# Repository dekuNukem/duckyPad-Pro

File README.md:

# duckyPad Pro: Advanced Macro Scripting Beyond QMK/VIA

[Get duckyPad Pro](https://www.tindie.com/products/37399/) | [Official Discord](https://discord.gg/4sJCBx5) | [Getting Started](./doc/getting_started.md) | [Table of Contents](#table-of-contents)

-----------

duckyPad Pro is a 20-key **mechanical macropad** for power users who demand **advanced macro scripting and customisation** beyond the shackles of QMK/VIA.

Using a [Turing-complete scripting language](https://dekunukem.github.io/duckyPad-Pro/doc/duckyscript_info.html) with **massive on-board storage**, it can automate **any keyboard/mouse input** you want, from **simple combos** to **full-blown programs**.

## Get One

duckyPad Pro has been [successfully funded on Kickstarter](https://www.kickstarter.com/projects/dekunukem/duckypad-pro-advanced-macro-scripting-beyond-qmk-via) with more than $100K raised!

* Now available [on my Store!](https://www.tindie.com/products/37399/)

No drivers needed. Works anywhere.

## Highlights

duckyPad Pro has all the basics:

* Hot-Swap
* Rotary Encoders (**Tactile or Smooth**)
* Per-key RGB
* 100% **Open-source**

But also features **unlike any other**:

* Custom **[duckyScript](https://dekunukem.github.io/duckyPad-Pro/doc/duckyscript_info.html)** engine, **NOT QMK/VIA**.
* **Longer and more complex** macros
	* **64 profiles**, 3712 macros.
* **OLED** screen
* **Bluetooth**
* Real-time Clock (RTC)
* **[Expansion Modules](https://github.com/dekuNukem/duckyPad-expansion-modules)** for external switches / foot pedals
* [Profile Auto-switching](https://github.com/dekuNukem/duckyPad-profile-autoswitcher) based on **active window**.
* microSD storage
* No proprietary drivers, works out-of-box.
* **Hacker friendly** with [tinkering guide](./doc/tinkering_guide.md)

## duckyScript vs QMK/VIA

duckyPad Pro runs **duckyScript**, originally designed for the [USB Rubber Ducky](https://shop.hak5.org/products/usb-rubber-ducky-deluxe).

Compared to QMK/VIA, you get:

* **Much Longer Macros**
	* [Entire Bee Movie](resources/beemovie.txt) in one macro? Sure thing!
	* Over 3700 macros total

* **Turing-Complete Scripting**
	* Variables, conditions, loops, functions, and more.
	* Executed on [32-bit Bytecode VM](https://duckypad.github.io/DuckStack/)
	* With **Scratch** and **Non-volatile Memory**

* **Advanced Interactions**
	* Reading Buttons
	* Print to OLED screen
	* Change RGB Color
	* How about a fully functional [Pong game?](resources/photos/pong.gif) [[code]](resources/pong.txt)

* **SD Card Storage**
	* Fast Configuration / Backup / Deployment
	* No sketchy drivers or apps
	* No recompiling

While QMK/VIA are great for regular keyboards, they are limited at input automations.

duckyScript is a no-brainer for **power users** with more demanding scripting needs.

## How It Works / Showcase

* Create up to **64 profiles**, one for each application.

* Assign up to **58 keys** per profile (20 onboard + 6 rotary encoder + 32 external)

* Names are shown on OLED screen

* Write a **duckyScript** for each key

### Easy Start

* **duckyScript** is a language for automating inputs

	* At simplest, you just tell it **what key to press!**

* Such as **key combos** of your favorite app

**Browsing**

Zoom In: `CTRL +`

Next Tab: `CTRL SHIFT TAB`

### Up a Notch

* Once familiar, you can write **longer multi-line macros** to further speed up everyday task.

* Such as **filling forms** and typing **boilerplate text** with one keypress.

```
STRING Michael Scott
TAB
STRING United States
ENTER
STRING 5705550100
TAB
STRING michael.scott@dundermifflin.com
TAB
```

Or a simple mouse jiggler:

```
WHILE TRUE
	MOUSE_MOVE $_RANDOM_INT $_RANDOM_INT
	DELAY 100
END_WHILE
```

### Full Potential

* Going all-out, duckyScript is a **Turing-Complete** **general-purpose** language.
* You can use it to:
	* Read Buttons
	* Write to OLED screen
	* Change RGB colors
	* Perform operations with **32-bit variables**, **conditions**, **loops**, **function call**s, and more!
* Write ultra-specific macros for your exact needs

```
RGB_SET 1 128 0 255

OLED_PRINT You are in a maze
OLED_PRINT of twisty little passages

VAR choice = _READKEY

IF choice == 1
    OLED_CURSOR 0 10
    OLED_PRINT It is a dead end.
    OLED_PRINT Something moves
    OLED_PRINT behind you.
END_IF
```

Or how about a fully working [Pong game?](resources/pong.txt)

```
WHILE TRUE
    active_key = _READKEY
    OLED_CLEAR
    draw_paddle()
    draw_court()
    draw_ball()
    OLED_UPDATE
    DELAY 20
END_WHILE
```

### Hackerman

* Of course, by automating inputs, you can take over an entire computer with the push of a button!

* This is known as [BadUSB attack](https://arstechnica.com/information-technology/2014/07/this-thumbdrive-hacks-computers-badusb-exploit-makes-devices-turn-evil/), and was the original purpose of [USB Rubber Ducky](https://shop.hak5.org/products/usb-rubber-ducky-deluxe).

---------

### Nothing Like It

* From **simple shortcuts** to **full-blown programs**, duckyScript can easily achieve what was impossible on QMK/VIA.

* Each macro can contain over **60,000 characters**

* Store over **3700 macros** in total

* Executed on custom [virtual stack machine](https://duckypad.github.io/DuckStack/)

## Bluetooth

duckyPad Pro also works as a **Bluetooth Keyboard & Mouse** (with a catch!)

* Bluetooth 5.0
* Built-in Antenna for both BT and Wi-Fi

**So what's the catch?**

* You need to provide your own USB battery bank

Yes I know it's a bit silly having BT without internal battery! However, it would involve more complex case design, additional components, and international shipping of rechargeable batteries.

All of which would inflate the cost way beyond just using an off-the-shelf battery pack.

As this is a one-person project, I prefer to keep things simple.

## Expansion Modules

duckyPad Pro also supports optional [expansion modules](https://github.com/dekuNukem/duckyPad-expansion-modules) for even more customisability.

* Wire up your own **switches / buttons / foot pedals**
* **8 channels** per module
* **Daisy-chain** up to 32 channels

## New CPU

duckyPad Pro now runs a significantly more powerful processor:

* ESP32-S3
* Dual-Core @ 240 MHz 
* 4MB Flash Memory
* 512KB RAM
* 2MB PSRAM

Switching to ESP32 also allows **much simpler setup for tinkering:**

* VSCode IDE
* Open-source toolchain
* USB Flashing, no external programmer needed.
* [Tinkering guide provided](./doc/tinkering_guide.md)

## QoL Updates

* Separate script for **on press** and **on release**
* **Abort execution** with any key
* Read `NUMLOCK` / `CAPSLOCK` / `SCROLLLOCK` status
* Switch profile by name (instead of number)
* Configurable screen orientation
* Mount SD Card as **USB Storage**
* Blocking `$_READKEY`
* Much faster configurator load/save
* **Drag & drop** firmware update
* More sturdy +/- button
* Reinforced hotswap socket solder pads
* A lot more under-the-hood optimizations

## duckyPad Configurator

[Use the open-source configurator](https://github.com/duckyPad/duckyPad-Configurator) to set up your duckyPad Pro.

* Windows | Mac | Linux
* No account / subscription needed
* No data collection / telemetry

## Profile Auto-switching

* [Automatically jump to the appropriate profile](https://github.com/dekuNukem/duckyPad-profile-autoswitcher)
* Based on **current active window**

## Mechanical Switches

duckyPad Pro has **20 Mechanical Switches** in **4x5 Grid.**

* Kailh hot-swap socket
* Cherry-MX compatible (Both 3 and 5-Pin)
* North-facing ARGB LED
* Configurable colour & brightness

## Rotary Encoders

* Two Encoders
* Bourns Inc. PEC12R Series
* Built-in Tactile Switch
* Max Knob Diameter: 24mm

## OLED Display

* 128x128
* 1.5 inch
* High contrast with true black
* **Configurable orientation**
* Burn-in Prevention

## Interested?

Available [on my store!](https://www.tindie.com/products/37399/)

Join our [Official Discord](https://discord.gg/4sJCBx5) for discussions and updates!

## Specifications

## Questions or Comments?

Please feel free to [open an issue](https://github.com/dekuNukem/duckypad-pro/issues), ask in the [official duckyPad discord](https://discord.gg/4sJCBx5), or email `dekuNukem`@`gmail`.`com`!

## Disclaimers

* duckyPad has been in active development since 2017, and every effort has been made to ensure its reliability. However, it is **NOT** designed or certified for safety-critical applications. Use at your own risk.

* Scripts are stored as **plain text** on the SD card. Keep in mind before including sensitive information.

* duckyScript appears to be a trademark of [Hak5 LLC](https://docs.hak5.org/hak5-usb-rubber-ducky/duckyscript-tm-quick-reference). The duckyPad project is not affiliated with, or endorsed by Hak5 LLC.

* The duckyScript [compiler and virtual machine](https://duckypad.github.io/DuckStack/) used in this project are independently developed from scratch.

## Table of Contents

[Main page](README.md)

[Getting Started Guide](./doc/getting_started.md)

[Kit Assembly Guide](./doc/kit_assembly.md)

[Writing duckyScript](./doc/duckyscript_info.md)

[duckStack VM](https://duckypad.github.io/DuckStack/)

[Tinkering Guide](./doc/tinkering_guide.md)

[Troubleshooting](./doc/troubleshooting.md)

[Firmware Update](./doc/fw_update.md)

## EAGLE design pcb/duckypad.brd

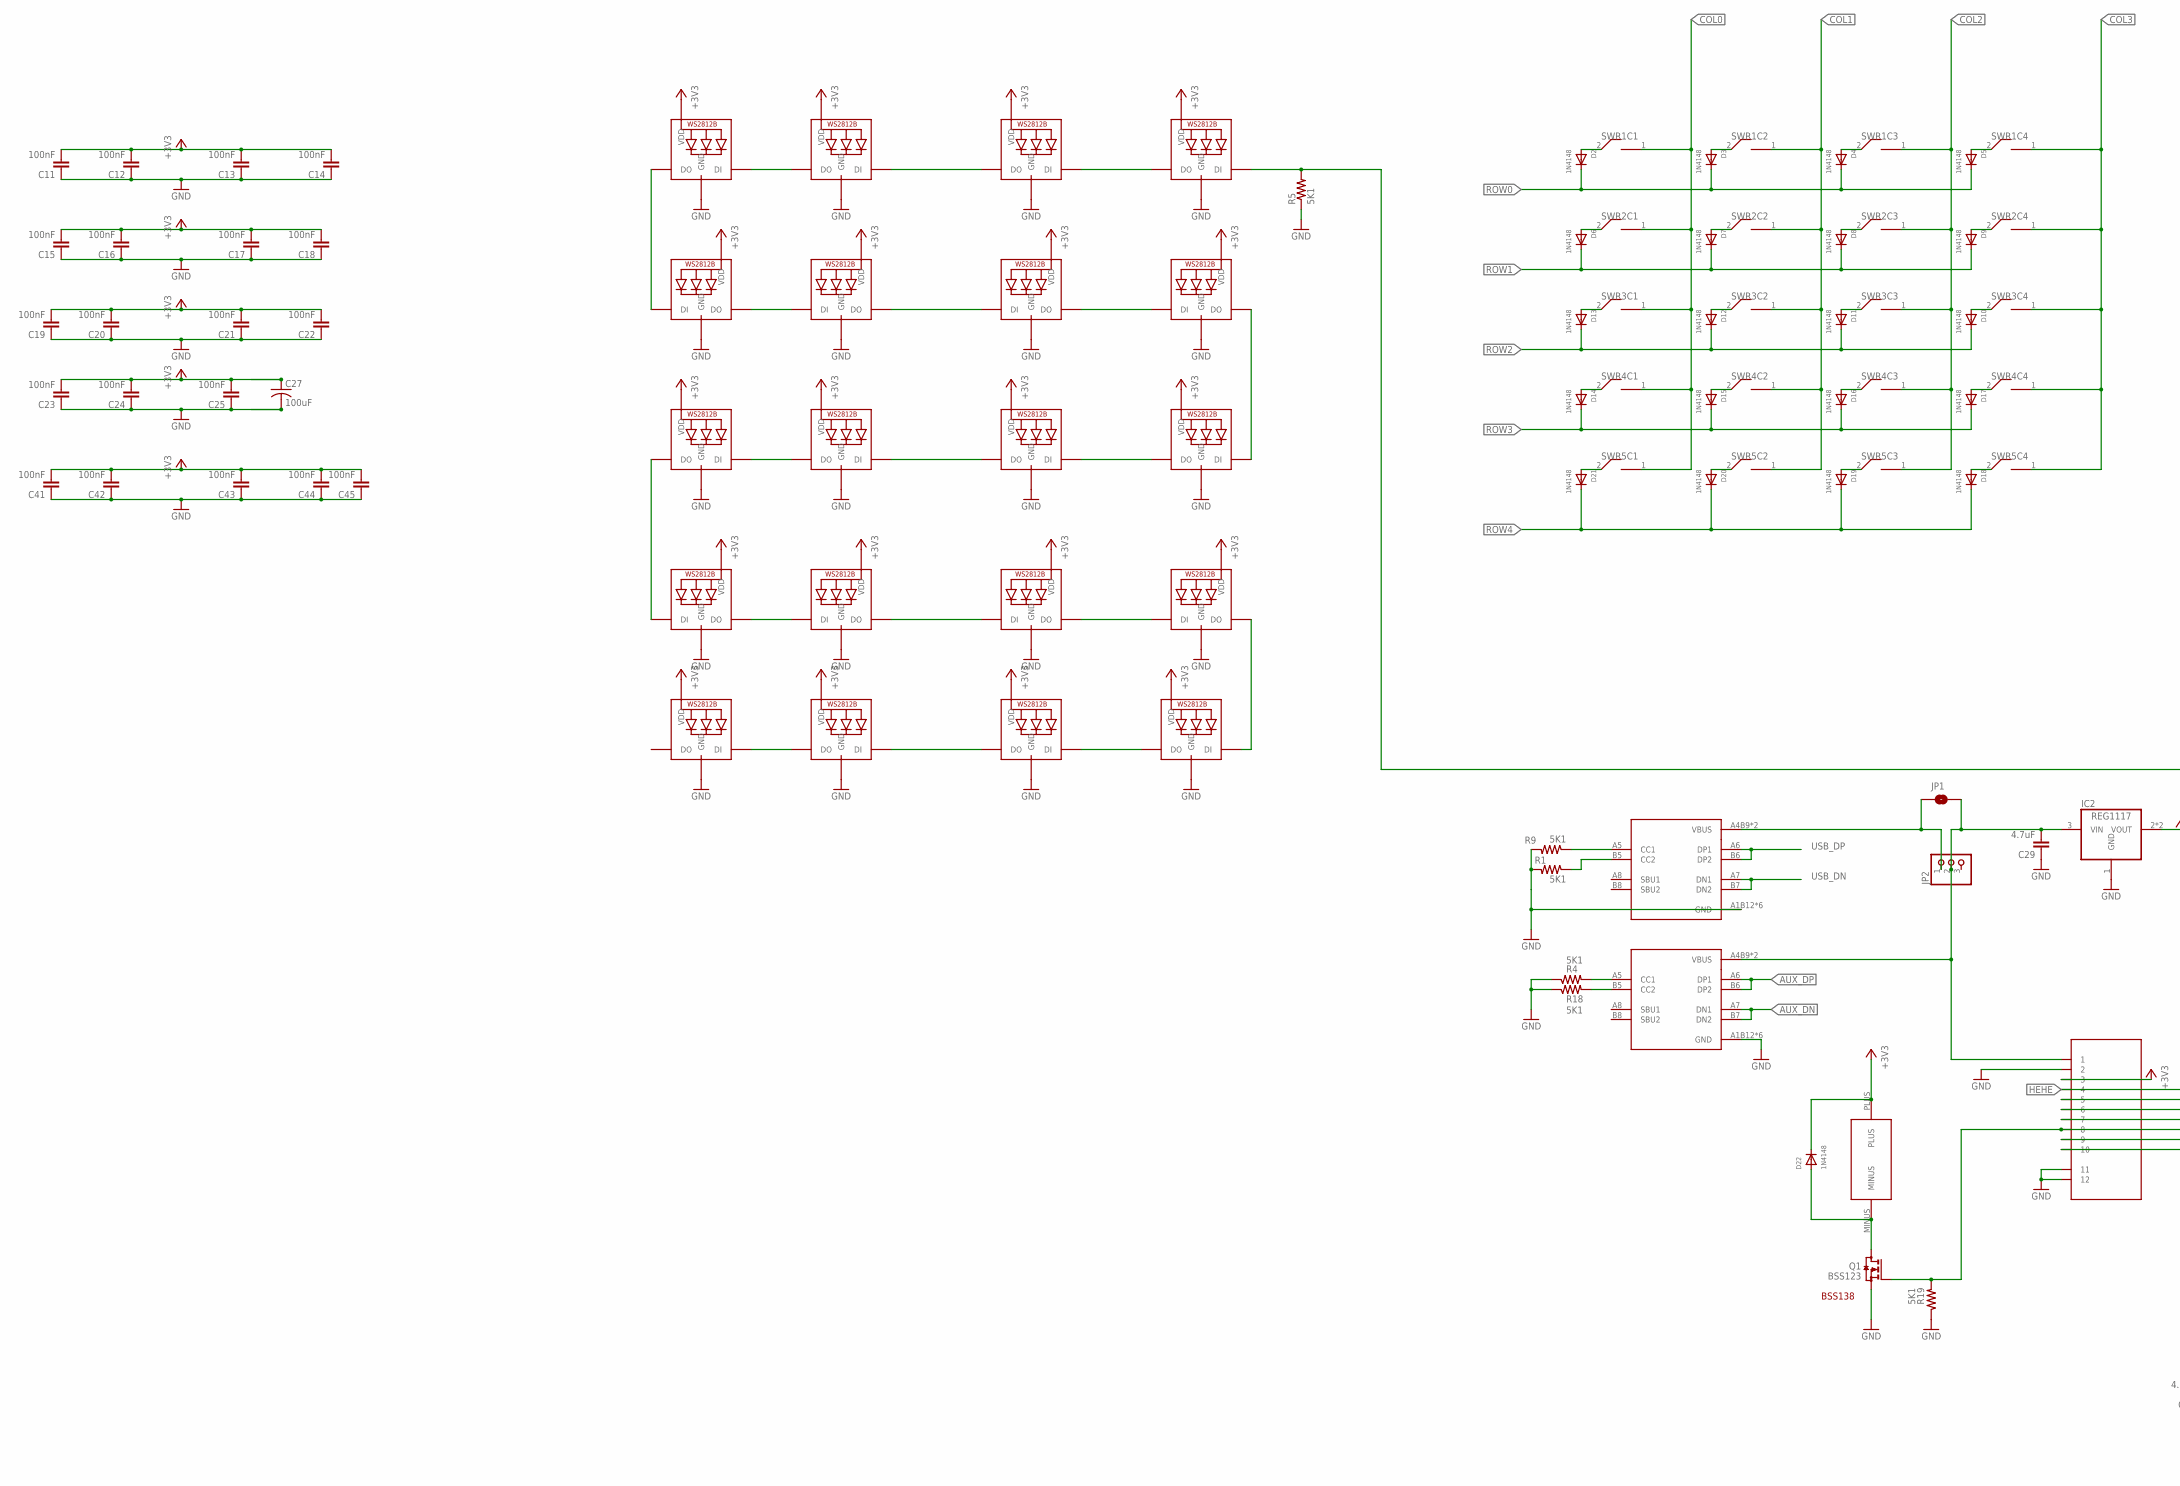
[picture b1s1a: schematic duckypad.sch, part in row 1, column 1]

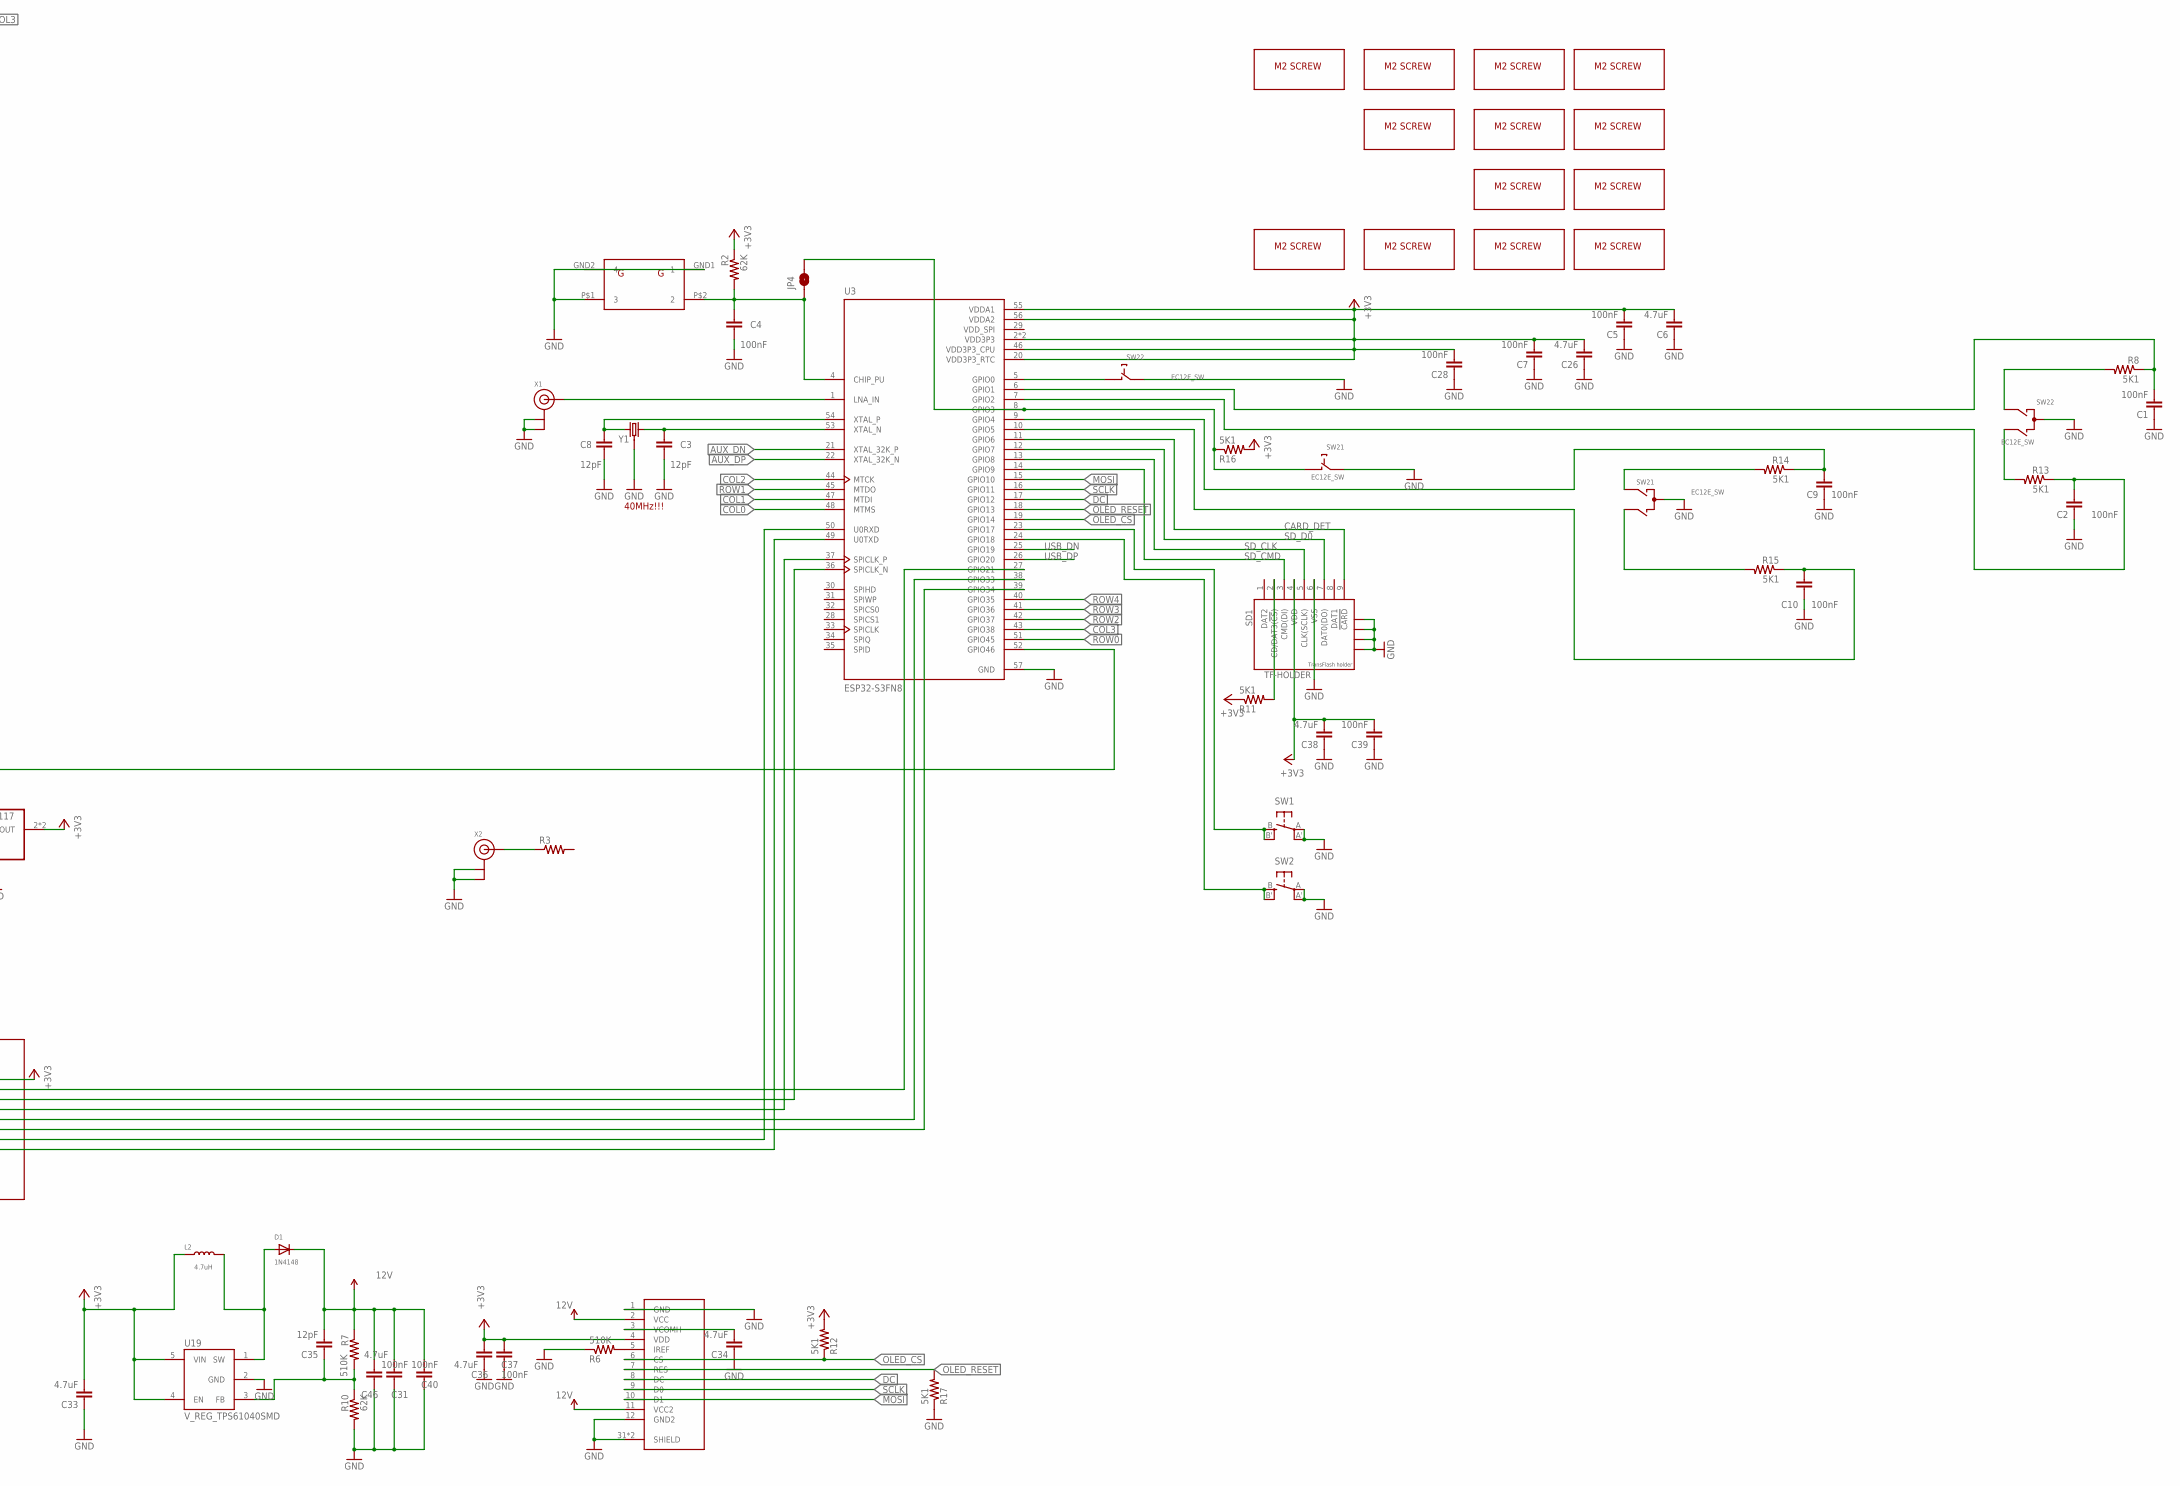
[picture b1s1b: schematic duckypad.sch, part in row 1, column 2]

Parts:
BZ1: BUZZ40402; BUZZ
C1, C2, C4, C5, C7, C9, C10, C11, C12, C13, C14, C15, C16, C17, C18, C19, C20, C21, C22, C23, C24, C25, C28, C31, C37, C39, C40, C41, C42, C43, C44, C45: 100nF; 0805
C3, C8, C35: 12pF; 0805
C6, C26, C29, C33, C34, C36, C38, C46: 4.7uF; 0805
C27: 100uF; C1210
D1, D2, D3, D4, D5, D6, D7, D8, D9, D10, D11, D12, D13, D14, D15, D16, D17, D18, D19, D20, D21, D22: 1N4148; ADAFRUIT_CHANGED_SOD-123
IC2: REG1117; SOT223
JP1, JP4: JUMPER-SMT_2_NO_NO-SILK; SMT-JUMPER_2_NO_NO-SILK
JP2: PINHD-1X3CB; 1X03-CLEANBIG
L2: 4.7uH; L4030
LED_R1C1, LED_R1C2, LED_R1C3, LED_R1C4, LED_R2C1, LED_R2C2, LED_R2C3, LED_R2C4, LED_R3C1, LED_R3C2, LED_R3C3, LED_R3C4, LED_R4C1, LED_R4C2, LED_R4C3, LED_R4C4, LED_R5C1, LED_R5C2, LED_R5C3, LED_R5C4: WS2812B; REVERSE_MNT
Q1: BSS123; SOT23
R1, R4, R5, R8, R9, R11, R12, R13, R14, R15, R16, R17, R18, R19: 5K1; 0805
R2, R10: 62K; 0805
R3: R-US_R2010; R2010
R6, R7: 510K; 0805
SD1: TF-HOLDER; TF-PULL
SH1: SH10P; DUCKYPAD_SM12B-SSR-H-TB
SW1, SW2: SPST_TACT-EVQQ2; EVQ-Q2
SW3: 3POS_SLIDE_SWITCH_324_SW; SIDEPUSH
SW21, SW22: EC12E_SW; ALPS_EC12E_SW
SWR1C1, SWR1C2, SWR1C3, SWR1C4, SWR2C1, SWR2C2, SWR2C3, SWR2C4, SWR3C1, SWR3C2, SWR3C3, SWR3C4, SWR4C1, SWR4C2, SWR4C3, SWR4C4, SWR5C1, SWR5C2, SWR5C3, SWR5C4: KAILH_SWITCH_SOCKET_KAILH_SWITCH_SOCKET; KAILH_SWITCH_SOCKET_SWITCH_SOCKET
U1, U2: USBC_16P; USBC_16P_FOOT
U3: ESP32-S3FN8; QFN40P700X700X90-57N
U19: V_REG_TPS61040SMD; SOT23-5
U$2: OLED_OLED128; OLED_LUL_UG-2864HSWEG01_1.3_WRAPAROUND
U$7, U$8, U$9, U$11, U$12, U$13, U$14, U$15, U$16, U$17, U$20, U$21, U$22: M2_SCREW_DEV; M2_SCREW_FOOT
X1, X2: ANTENNA_U.FL; U.FL
Y1: 16MHz_12pF; CRYSTAL-SMD-3.2X2.5MM

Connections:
12V: C31.2, C35.2, C40.2, C46.2, D1.C, R7.1, U$2.2 (VCC), U$2.11 (VCC2)
+3V3: BZ1.PLUS, C5.2, C6.2, C7.2, C11.2, C12.2, C13.2, C14.2, C15.2, C16.2, C17.2, C18.2, C19.2, C20.2, C21.2, C22.2, C23.2, C24.2, C25.2, C26.2, C27.1, C28.2, C33.2, C36.2, C37.2, C38.2, C39.2, C41.2, C42.2, C43.2, C44.2, C45.2, D22.C, IC2.2 (VOUT), IC2.4 (VOUT), L2.1, LED_R1C1.VDD, LED_R1C2.VDD, LED_R1C3.VDD, LED_R1C4.VDD, LED_R2C1.VDD, LED_R2C2.VDD, LED_R2C3.VDD, LED_R2C4.VDD, LED_R3C1.VDD, LED_R3C2.VDD, LED_R3C3.VDD, LED_R3C4.VDD, LED_R4C1.VDD, LED_R4C2.VDD, LED_R4C3.VDD, LED_R4C4.VDD, LED_R5C1.VDD, LED_R5C2.VDD, LED_R5C3.VDD, LED_R5C4.VDD, R2.1, R11.1, R12.2, R16.2, SD1.4 (VDD), SH1.3, U3.2 (VDD3P3), U3.3 (VDD3P3), U3.20 (VDD3P3_RTC), U3.46 (VDD3P3_CPU), U3.55 (VDDA1), U3.56 (VDDA2), U19.4 (EN), U19.5 (VIN), U$2.4 (VDD)
AUX_DN: U1.A7 (DN1), U1.B7 (DN2), U3.21 (XTAL_32K_P)
AUX_DP: U1.A6 (DP1), U1.B6 (DP2), U3.22 (XTAL_32K_N)
CARD_DET: SD1.9 (!CARD), U3.11 (GPIO6)
COL0: SWR1C1.1 (2), SWR2C1.1 (2), SWR3C1.1 (2), SWR4C1.1 (2), SWR5C1.1 (2), U3.48 (MTMS)
COL1: SWR1C2.1 (2), SWR2C2.1 (2), SWR3C2.1 (2), SWR4C2.1 (2), SWR5C2.1 (2), U3.47 (MTDI)
COL2: SWR1C3.1 (2), SWR2C3.1 (2), SWR3C3.1 (2), SWR4C3.1 (2), SWR5C3.1 (2), U3.44 (MTCK)
COL3: SWR1C4.1 (2), SWR2C4.1 (2), SWR3C4.1 (2), SWR4C4.1 (2), SWR5C4.1 (2), U3.43 (GPIO38)
DC: U3.17 (GPIO12), U$2.8 (DC)
GND: C1.1, C2.1, C3.2, C4.2, C5.1, C6.1, C7.1, C8.2, C9.1, C10.1, C11.1, C12.1, C13.1, C14.1, C15.1, C16.1, C17.1, C18.1, C19.1, C20.1, C21.1, C22.1, C23.1, C24.1, C25.1, C26.1, C27.2, C28.1, C29.1, C31.1, C33.1, C34.1, C36.1, C37.1, C38.1, C39.1, C40.1, C41.1, C42.1, C43.1, C44.1, C45.1, C46.1, IC2.1 (GND), LED_R1C1.GND, LED_R1C2.GND, LED_R1C3.GND, LED_R1C4.GND, LED_R2C1.GND, LED_R2C2.GND, LED_R2C3.GND, LED_R2C4.GND, LED_R3C1.GND, LED_R3C2.GND, LED_R3C3.GND, LED_R3C4.GND, LED_R4C1.GND, LED_R4C2.GND, LED_R4C3.GND, LED_R4C4.GND, LED_R5C1.GND, LED_R5C2.GND, LED_R5C3.GND, LED_R5C4.GND, Q1.2 (S), R1.2, R4.1, R5.1, R6.1, R9.2, R10.2, R17.1, R18.1, R19.1, SD1.6 (VSS), SD1.S1, SD1.S2, SD1.S3, SD1.S4, SH1.2, SH1.FIT@1 (11), SH1.FIT@2 (12), SW1.A, SW1.A' (P1), SW2.A, SW2.A' (P1), SW3.GND1 (1), SW3.GND2 (4), SW3.P$1 (3), SW21.C, SW21.E (2), SW22.C, SW22.E (2), U1.A1B12 (GND), U1.B11A12 (GND), U1.P$13 (GND), U1.P$14 (GND), U1.P$15 (GND), U1.P$16 (GND), U2.A1B12 (GND), U2.B11A12 (GND), U2.P$13 (GND), U2.P$14 (GND), U2.P$15 (GND), U2.P$16 (GND), U3.57 (GND), U19.2 (GND), U$2.1 (GND), U$2.12 (GND2), U$2.31 (SHIELD), U$2.32 (SHIELD), X1.1 (GND), X1.2 (GND), X2.1 (GND), X2.2 (GND), Y1.2 (3), Y1.4 (3)
HEHE: SH1.4, U3.27 (GPIO21)
MOSI: U3.15 (GPIO10), U$2.10 (D1)
unnamed: JP1.1, JP2.1, U2.A4B9 (VBUS), U2.B4A9 (VBUS)
unnamed: LED_R1C3.DIN (DI), LED_R1C4.DOUT (DO)
unnamed: LED_R1C2.DIN (DI), LED_R1C3.DOUT (DO)
unnamed: LED_R1C1.DIN (DI), LED_R1C2.DOUT (DO)
unnamed: LED_R1C1.DOUT (DO), LED_R2C1.DIN (DI)
unnamed: LED_R2C1.DOUT (DO), LED_R2C2.DIN (DI)
unnamed: LED_R2C2.DOUT (DO), LED_R2C3.DIN (DI)
unnamed: C34.2, U$2.3 (VCOMH)
unnamed: LED_R2C3.DOUT (DO), LED_R2C4.DIN (DI)
unnamed: R6.2, U$2.5 (IREF)
unnamed: LED_R2C4.DOUT (DO), LED_R3C4.DIN (DI)
unnamed: LED_R3C3.DIN (DI), LED_R3C4.DOUT (DO)
unnamed: LED_R3C2.DIN (DI), LED_R3C3.DOUT (DO)
unnamed: C9.2, R14.1, U3.9 (GPIO4)
unnamed: LED_R3C1.DIN (DI), LED_R3C2.DOUT (DO)
unnamed: LED_R3C1.DOUT (DO), LED_R4C1.DIN (DI)
unnamed: LED_R4C1.DOUT (DO), LED_R4C2.DIN (DI)
unnamed: LED_R4C2.DOUT (DO), LED_R4C3.DIN (DI)
unnamed: LED_R4C3.DOUT (DO), LED_R4C4.DIN (DI)
unnamed: LED_R4C4.DOUT (DO), LED_R5C4.DIN (DI)
unnamed: LED_R5C3.DIN (DI), LED_R5C4.DOUT (DO)
unnamed: LED_R5C2.DIN (DI), LED_R5C3.DOUT (DO)
unnamed: LED_R5C1.DIN (DI), LED_R5C2.DOUT (DO)
unnamed: C8.1, U3.54 (XTAL_P), Y1.1
unnamed: C3.1, U3.53 (XTAL_N), Y1.3 (2)
unnamed: U3.1 (LNA_IN), X1.3 (SIGNAL)
unnamed: D5.A, SWR1C4.2 (1)
unnamed: SW22.D (1), U3.5 (GPIO0)
unnamed: LED_R1C4.DIN (DI), R5.2, U3.52 (GPIO46)
unnamed: SW1.B (S), SW1.B' (S1), U3.23 (GPIO17)
unnamed: R1.1, U2.B5 (CC2)
unnamed: R4.2, U1.A5 (CC1)
unnamed: R9.1, U2.A5 (CC1)
unnamed: R8.2, SW22.A
unnamed: R13.2, SW22.B
unnamed: D1.A, L2.2, U19.1 (SW)
unnamed: BZ1.MINUS, D22.A, Q1.3 (D)
unnamed: C1.2, R8.1, U3.6 (GPIO1)
unnamed: C35.1, R7.2, R10.1, U19.3 (FB)
unnamed: C2.2, R13.1, U3.7 (GPIO2)
unnamed: JP4.2, R16.1, SW21.D (1), U3.8 (GPIO3)
unnamed: R15.2, SW21.B
unnamed: R11.2, SD1.2 (CD/DAT3(!CS!))
unnamed: D4.A, SWR1C3.2 (1)
unnamed: D3.A, SWR1C2.2 (1)
unnamed: D2.A, SWR1C1.2 (1)
unnamed: D9.A, SWR2C4.2 (1)
unnamed: R14.2, SW21.A
unnamed: C10.2, R15.1, U3.10 (GPIO5)
unnamed: D8.A, SWR2C3.2 (1)
unnamed: D7.A, SWR2C2.2 (1)
unnamed: D6.A, SWR2C1.2 (1)
unnamed: D10.A, SWR3C4.2 (1)
unnamed: D11.A, SWR3C3.2 (1)
unnamed: D12.A, SWR3C2.2 (1)
unnamed: D13.A, SWR3C1.2 (1)
unnamed: D17.A, SWR4C4.2 (1)
unnamed: D16.A, SWR4C3.2 (1)
unnamed: D15.A, SWR4C2.2 (1)
unnamed: D14.A, SWR4C1.2 (1)
unnamed: D18.A, SWR5C4.2 (1)
unnamed: D19.A, SWR5C3.2 (1)
unnamed: D20.A, SWR5C2.2 (1)
unnamed: D21.A, SWR5C1.2 (1)
unnamed: SW2.B (S), SW2.B' (S1), U3.24 (GPIO18)
unnamed: C29.2, IC2.3 (VIN), JP1.2, JP2.2, SH1.1, U1.A4B9 (VBUS), U1.B4A9 (VBUS)
unnamed: SH1.5, U3.36 (SPICLK_N)
unnamed: SH1.6, U3.37 (SPICLK_P)
unnamed: SH1.7, U3.38 (GPIO33)
unnamed: Q1.1 (G), R19.2, SH1.8, U3.39 (GPIO34)
unnamed: R3.1, X2.3 (SIGNAL)
unnamed: SH1.9, U3.50 (U0RXD)
unnamed: SH1.10, U3.49 (U0TXD)
unnamed: R18.2, U1.B5 (CC2)
OLED_CS: R12.1, U3.19 (GPIO14), U$2.6 (CS)
OLED_RESET: R17.2, U3.18 (GPIO13), U$2.7 (RES)
RESET: C4.1, JP4.1, R2.2, SW3.P$2 (2), U3.4 (CHIP_PU)
ROW0: D2.C, D3.C, D4.C, D5.C, U3.51 (GPIO45)
ROW1: D6.C, D7.C, D8.C, D9.C, U3.45 (MTDO)
ROW2: D10.C, D11.C, D12.C, D13.C, U3.42 (GPIO37)
ROW3: D14.C, D15.C, D16.C, D17.C, U3.41 (GPIO36)
ROW4: D18.C, D19.C, D20.C, D21.C, U3.40 (GPIO35)
SCLK: U3.16 (GPIO11), U$2.9 (D0)
SD_CLK: SD1.5 (CLK(SCLK)), U3.13 (GPIO8)
SD_CMD: SD1.3 (CMD(DI)), U3.14 (GPIO9)
SD_D0: SD1.7 (DAT0(DO)), U3.12 (GPIO7)
USB_DN: U2.A7 (DN1), U2.B7 (DN2), U3.25 (GPIO19)
USB_DP: U2.A6 (DP1), U2.B6 (DP2), U3.26 (GPIO20)
VDD_SPI: U3.29 (VDD_SPI)

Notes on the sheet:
40MHz!!!
BSS138

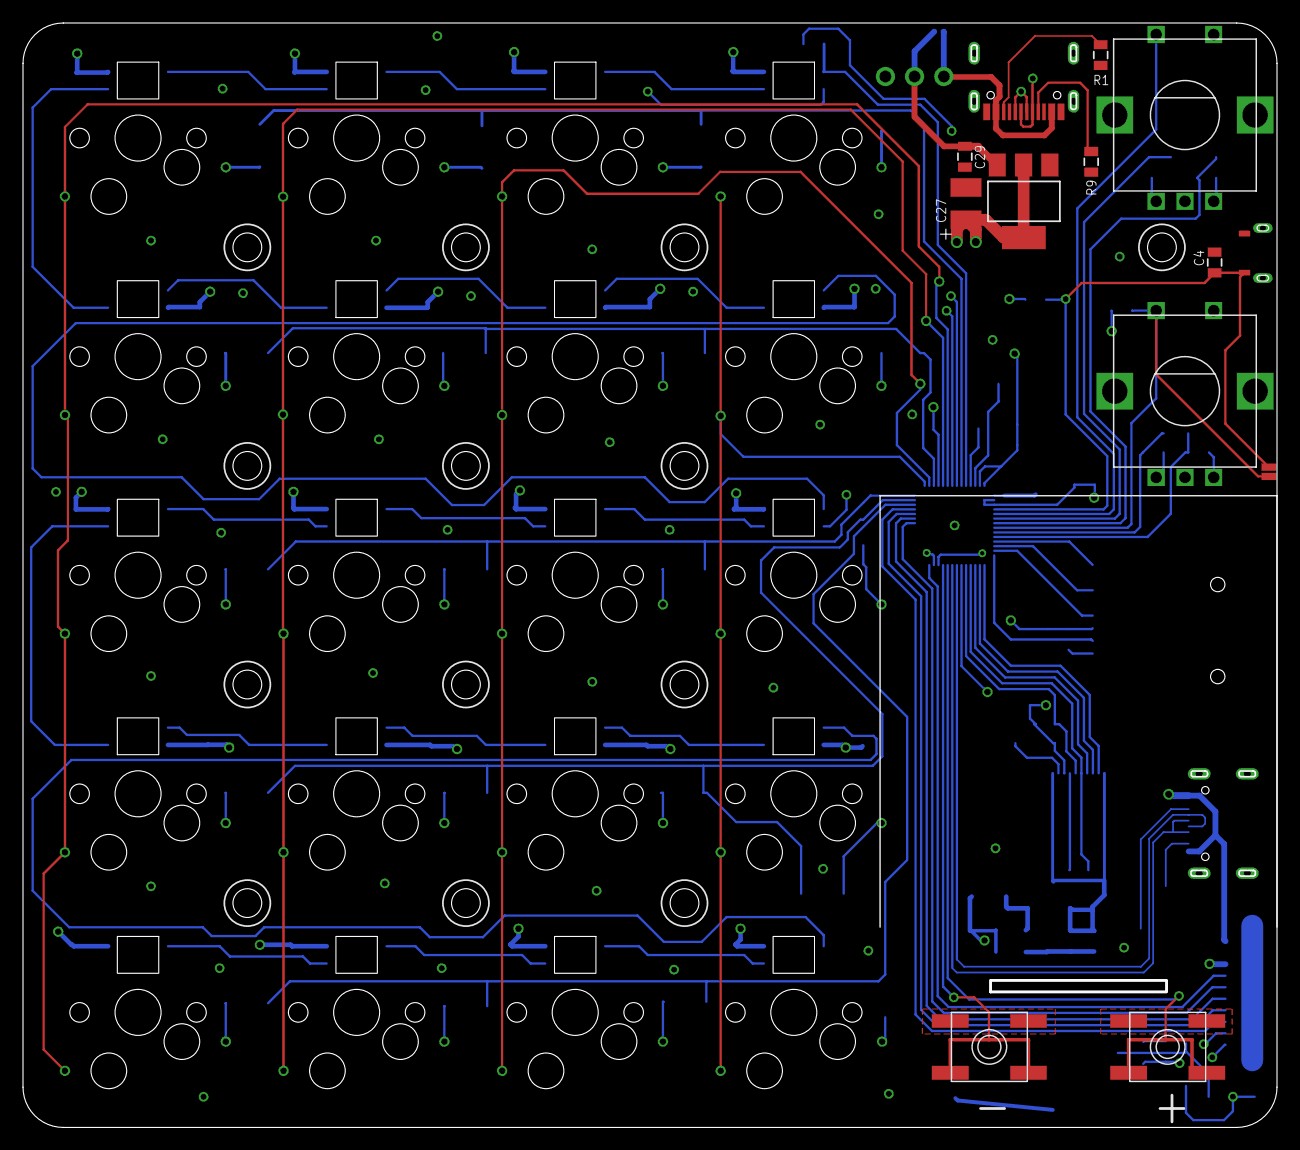
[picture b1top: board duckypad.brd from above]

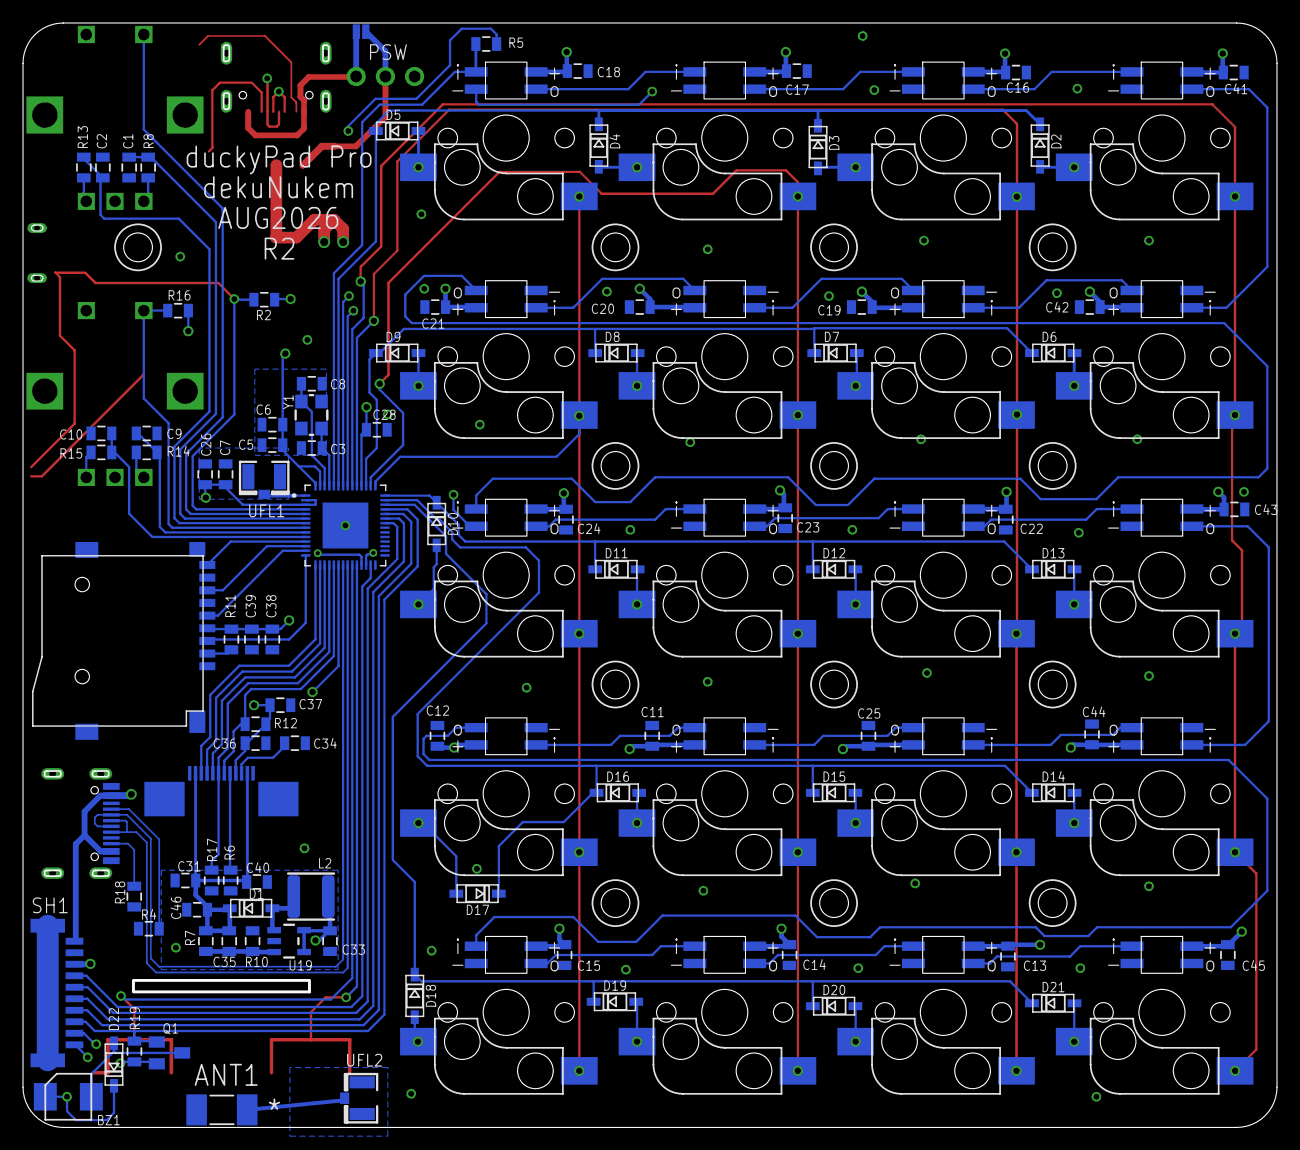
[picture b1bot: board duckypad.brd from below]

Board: 4 copper layers, 109.0 x 96.0 mm, 160 parts (93 on the bottom side), 101 nets.

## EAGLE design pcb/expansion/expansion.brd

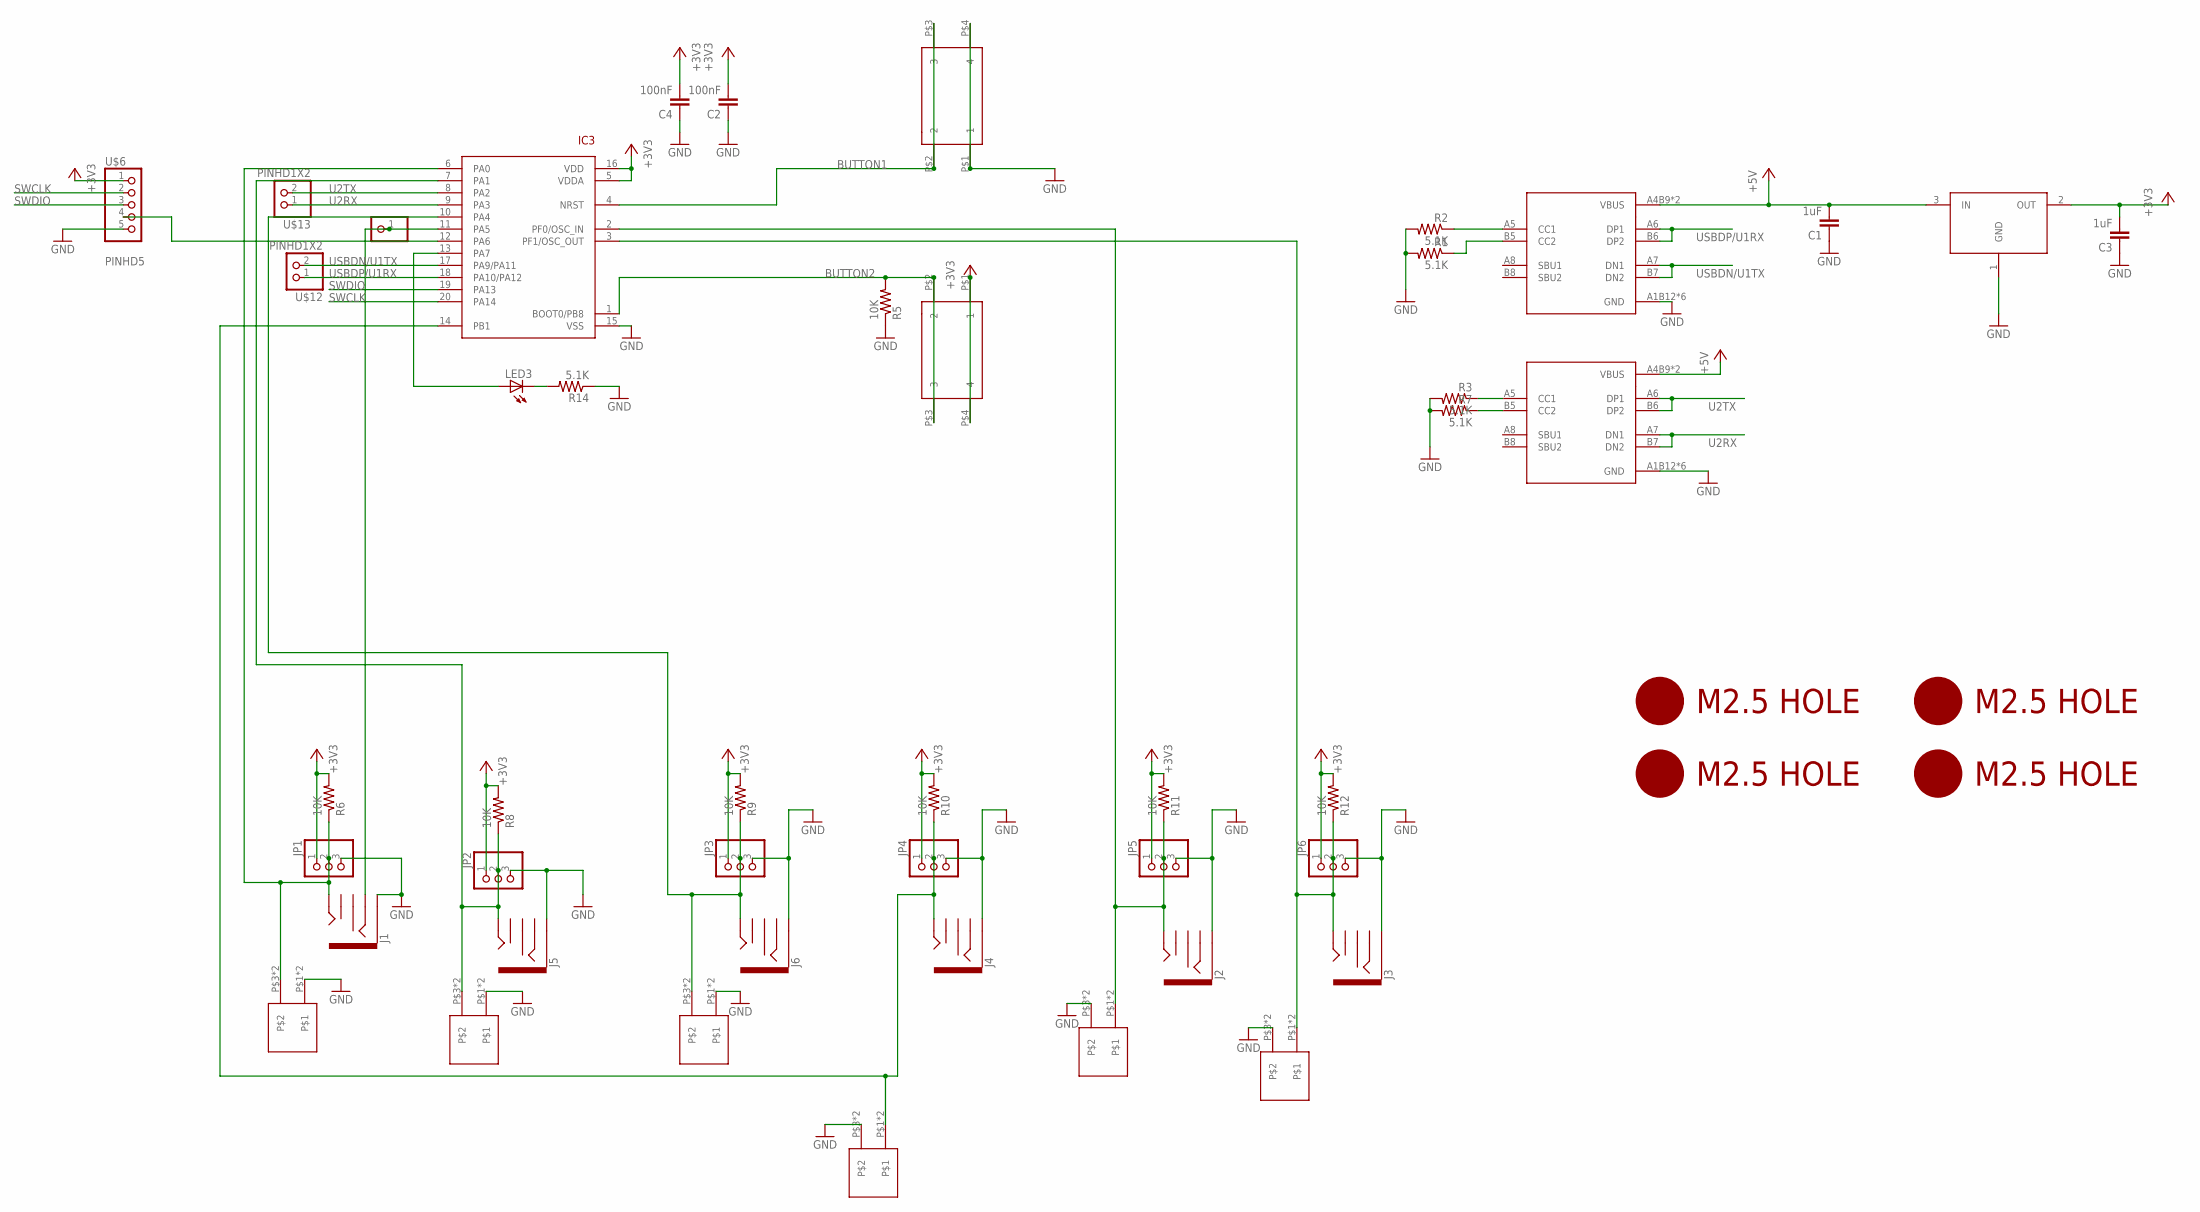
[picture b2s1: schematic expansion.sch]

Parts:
C1, C3: 1uF; 0805
C2, C4: 100nF; 0805
IC3: STM32F042F4; TSSOP20
J1, J2, J3, J4, J5, J6: AUDIO_JACK_3.5MM_PTH; AUDIO-JACK
JP1, JP2, JP3, JP4, JP5, JP6: PINHD-1X3; 1X03
JP7: PINHD-1X1CB; 1X01-CLEANBIG
LED3: LEDCHIP-LED0805; CHIP-LED0805
R1, R2, R3, R7, R14: 5.1K; 0805
R5, R6, R8, R9, R10, R11, R12: 10K; 0805
SW3, SW4: 324_SW; 342_SWICH_FOOT
U1, U2: USBC_16P; USBC_16P_FOOT
U4: XC6206_DEV; SOT23R_INFINEON
U$1, U$2, U$3, U$4, U$5, U$7: DG2204R-2
U$6: PINHD5; 1X05
U$8, U$9, U$10, U$11: M2.5HOLE
U$12, U$13: PINHD1X2; 1X02

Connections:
+3V3: C2.2, C3.2, C4.2, IC3.5 (VDDA), IC3.16 (VDD), JP1.1, JP2.1, JP3.1, JP4.1, JP5.1, JP6.1, R6.2, R8.2, R9.2, R10.2, R11.2, R12.2, SW4.P$1 (1), SW4.P$4 (4), U4.2 (OUT), U$6.1
+5V: C1.2, U1.A4B9 (VBUS), U1.B4A9 (VBUS), U2.A4B9 (VBUS), U2.B4A9 (VBUS), U4.3 (IN)
BUTTON1: IC3.4 (NRST), SW3.P$2 (2), SW3.P$3 (3)
BUTTON2: IC3.1 (BOOT0/PB8), R5.2, SW4.P$2 (2), SW4.P$3 (3)
CH1: IC3.6 (PA0), J1.TIP, JP1.2, R6.1, U$4.P$3, U$4.P$4
CH2: IC3.7 (PA1), J5.TIP, JP2.2, R8.1, U$5.P$3, U$5.P$4
CH3: IC3.10 (PA4), J6.TIP, JP3.2, R9.1, U$7.P$3, U$7.P$4
CH4: IC3.14 (PB1), J4.TIP, JP4.2, R10.1, U$1.P$1, U$1.P$2
CH5: IC3.2 (PF0/OSC_IN), J2.TIP, JP5.2, R11.1, U$2.P$1, U$2.P$2
CH6: IC3.3 (PF1/OSC_OUT), J3.TIP, JP6.2, R12.1, U$3.P$1, U$3.P$2
GND: C1.1, C2.1, C3.1, C4.1, IC3.15 (VSS), J1.SLEEVE, J2.SLEEVE, J3.SLEEVE, J4.SLEEVE, J5.SLEEVE, J6.SLEEVE, JP1.3, JP2.3, JP3.3, JP4.3, JP5.3, JP6.3, R1.2, R2.2, R3.2, R5.1, R7.2, R14.1, SW3.P$1 (1), SW3.P$4 (4), U1.A1B12 (GND), U1.B11A12 (GND), U1.P$13 (GND), U1.P$14 (GND), U1.P$15 (GND), U1.P$16 (GND), U2.A1B12 (GND), U2.B11A12 (GND), U2.P$13 (GND), U2.P$14 (GND), U2.P$15 (GND), U2.P$16 (GND), U4.1 (GND), U$1.P$3, U$1.P$4, U$2.P$3, U$2.P$4, U$3.P$3, U$3.P$4, U$4.P$1, U$4.P$2, U$5.P$1, U$5.P$2, U$6.5, U$7.P$1, U$7.P$2
unnamed: R3.1, U1.A5 (CC1)
unnamed: R7.1, U1.B5 (CC2)
unnamed: LED3.C, R14.2
unnamed: IC3.13 (PA7), LED3.A
unnamed: IC3.11 (PA5), J1.RING, JP7.1
unnamed: IC3.12 (PA6), U$6.4
unnamed: R1.1, U2.B5 (CC2)
unnamed: R2.1, U2.A5 (CC1)
SWCLK: IC3.20 (PA14), U$6.2
SWDIO: IC3.19 (PA13), U$6.3
U2RX: IC3.9 (PA3), U1.A7 (DN1), U1.B7 (DN2), U$13.1
U2TX: IC3.8 (PA2), U1.A6 (DP1), U1.B6 (DP2), U$13.2
USBDN/U1TX: IC3.17 (PA9/PA11), U2.A7 (DN1), U2.B7 (DN2), U$12.2
USBDP/U1RX: IC3.18 (PA10/PA12), U2.A6 (DP1), U2.B6 (DP2), U$12.1

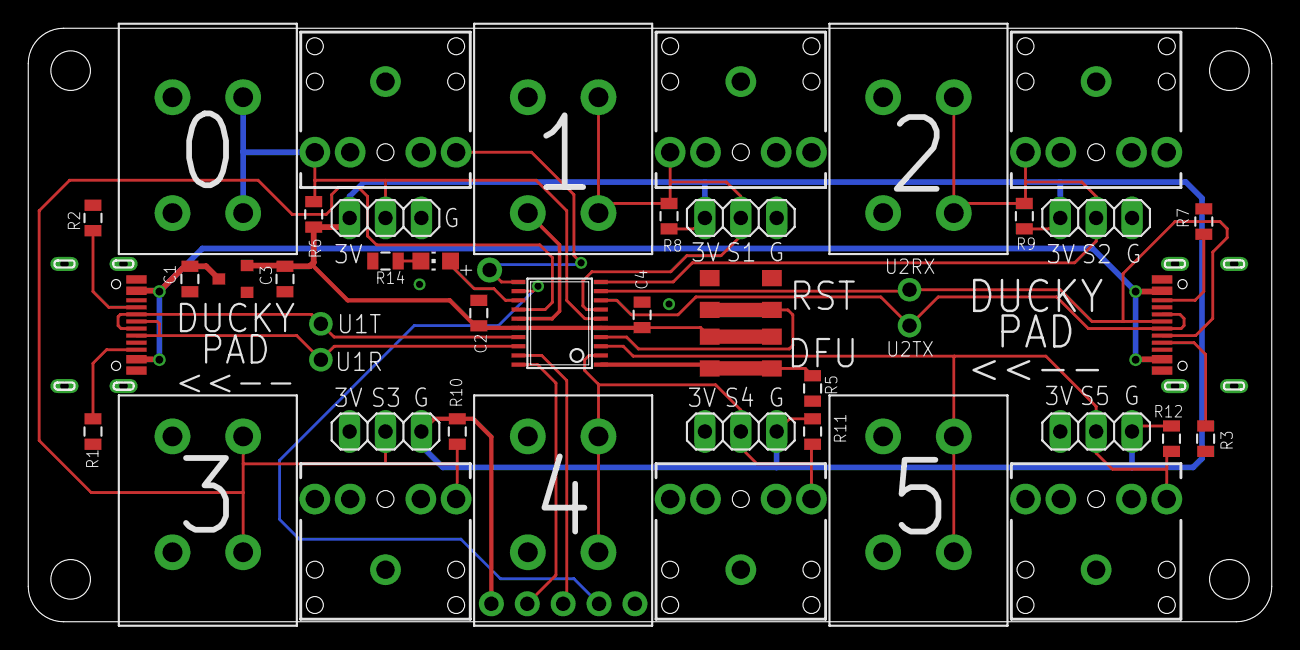
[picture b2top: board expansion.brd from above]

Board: 2 copper layers, 88.0 x 42.0 mm, 49 parts (0 on the bottom side), 25 nets.

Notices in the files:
parts and their libraries:
SparkFun-Clocks: Licensing: Creative Commons ShareAlike 4.0 International - https://creativecommons.org/licenses/by-sa/4.0
microbuilder: This work is placed in the public domain, and may be freely used for commercial and non-commercial work with the following conditions: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
